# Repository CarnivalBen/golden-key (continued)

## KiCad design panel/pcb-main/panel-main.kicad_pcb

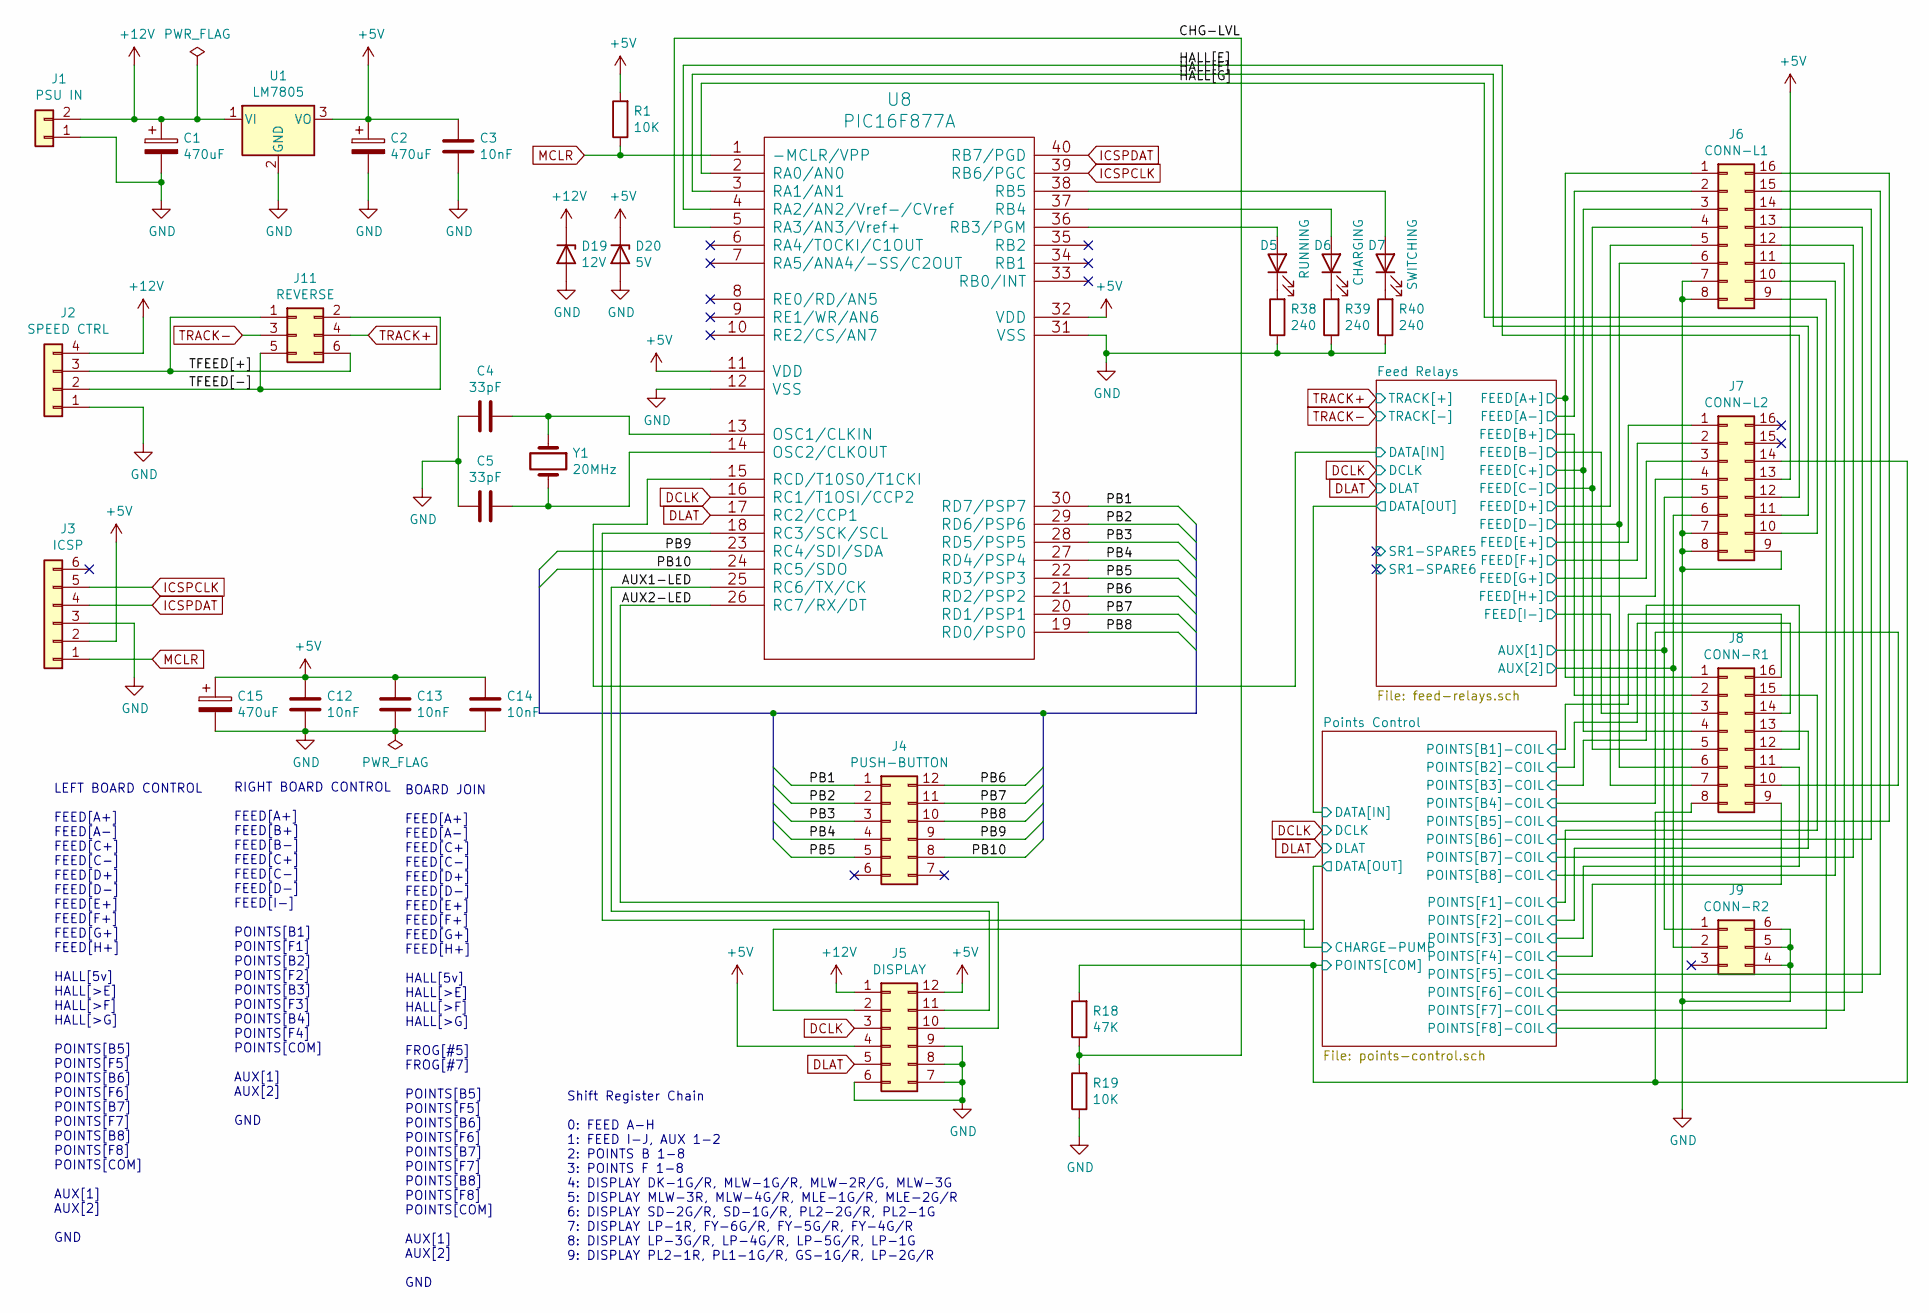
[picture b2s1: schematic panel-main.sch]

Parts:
C1, C2, C15: 470uF; CP_Radial_D10.0mm_P5.00mm
C3, C12, C13, C14: 10nF; C_Disc_D4.7mm_W2.5mm_P5.00mm
C4, C5: 33pF; C_Disc_D3.4mm_W2.1mm_P2.50mm
D5: RUNNING; LED_D5.0mm
D6: CHARGING; LED_D5.0mm
D7: SWITCHING; LED_D5.0mm
D19: 12V; D_DO-15_P10.16mm_Horizontal
D20: 5V; D_DO-15_P10.16mm_Horizontal
J1: PSU IN; Wire_Pads_Edge_1x2
J2: SPEED CTRL; DIN_Socket_Edge_Solder_4pin
J3: ICSP; Pin_Header_Straight_1x06_Pitch2.54mm
J4: PUSH-BUTTON; Pin_Header_Straight_2x06_Pitch2.54mm
J5: DISPLAY; Pin_Header_Straight_2x06_Pitch2.54mm
J6: CONN-L1; Wire_Pads_Edge_2x8
J7: CONN-L2; Wire_Pads_Edge_2x8
J8: CONN-R1; Wire_Pads_Edge_2x8
J9: CONN-R2; Wire_Pads_Edge_2x3
J11: REVERSE; Pin_Header_Straight_2x03_Pitch2.54mm
R1, R19: 10K; R_Axial_DIN0207_L6.3mm_D2.5mm_P10.16mm_Horizontal
R18: 47K; R_Axial_DIN0207_L6.3mm_D2.5mm_P10.16mm_Horizontal
R38, R39, R40: 240; R_Axial_DIN0207_L6.3mm_D2.5mm_P10.16mm_Horizontal
U1: LM7805; TO-220-3_Horizontal
U8: PIC16F877A; DIP-40_W15.24mm_LongPads
Y1: 20MHz; Crystal_HC49-U_Vertical

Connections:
+5V: C2.1, C3.1, C12.1, C13.1, C14.1, C15.1, D20.1 (K), J3.2, J5.4, J5.12, J7.13, R1.2, U1.3 (VO), U8.11 (VDD), U8.32 (VDD); also elsewhere on the board
+12V: C1.1, D19.1 (K), J1.2, J2.4, J5.1, U1.1 (VI); also elsewhere on the board
/AUX1-LED: J5.11, U8.25 (RC6/TX/CK)
/AUX2-LED: J5.10, U8.26 (RC7/RX/DT)
/CHG-LVL: R18.1, R19.2, U8.5 (RA3/AN3/Vref+)
/Feed Relays/AUX[1]: J7.5, J9.1; also elsewhere on the board
/Feed Relays/AUX[2]: J7.6, J9.2; also elsewhere on the board
/Feed Relays/DATA[IN]: U8.15 (RCD/T10S0/T1CKI); also elsewhere on the board
/Feed Relays/FEED[A+]: J6.1, J8.1; also elsewhere on the board
/Feed Relays/FEED[A-]: J6.2; also elsewhere on the board
/Feed Relays/FEED[B+]: J8.2; also elsewhere on the board
/Feed Relays/FEED[B-]: J8.3; also elsewhere on the board
/Feed Relays/FEED[C+]: J6.3, J8.4; also elsewhere on the board
/Feed Relays/FEED[C-]: J6.4, J8.5; also elsewhere on the board
/Feed Relays/FEED[D+]: J6.5; also elsewhere on the board
/Feed Relays/FEED[D-]: J6.6, J8.6; also elsewhere on the board
/Feed Relays/FEED[E+]: J7.1; also elsewhere on the board
/Feed Relays/FEED[F+]: J7.2; also elsewhere on the board
/Feed Relays/FEED[G+]: J7.3; also elsewhere on the board
/Feed Relays/FEED[H+]: J7.4; also elsewhere on the board
/Feed Relays/FEED[I-]: J8.7; also elsewhere on the board
/HALL[E]: J7.12, U8.4 (RA2/AN2/Vref-/CVref)
/HALL[F]: J7.11, U8.3 (RA1/AN1)
/HALL[G]: J7.10, U8.2 (RA0/AN0)
/PB1: J4.1, U8.30 (RD7/PSP7)
/PB2: J4.2, U8.29 (RD6/PSP6)
/PB3: J4.3, U8.28 (RD5/PSP5)
/PB4: J4.4, U8.27 (RD4/PSP4)
/PB5: J4.5, U8.22 (RD3/PSP3)
/PB6: J4.12, U8.21 (RD2/PSP2)
/PB7: J4.11, U8.20 (RD1/PSP1)
/PB8: J4.10, U8.19 (RD0/PSP0)
/PB9: J4.9, U8.23 (RC4/SDI/SDA)
/PB10: J4.8, U8.24 (RC5/SDO)
/Points Control/CHARGE-PUMP: U8.18 (RC3/SCK/SCL); also elsewhere on the board
/Points Control/DATA[OUT]: J5.2; also elsewhere on the board
/Points Control/POINTS[B1]-COIL: J8.16; also elsewhere on the board
/Points Control/POINTS[B2]-COIL: J8.14; also elsewhere on the board
/Points Control/POINTS[B3]-COIL: J8.12; also elsewhere on the board
/Points Control/POINTS[B4]-COIL: J8.10; also elsewhere on the board
/Points Control/POINTS[B5]-COIL: J6.16; also elsewhere on the board
/Points Control/POINTS[B6]-COIL: J6.14; also elsewhere on the board
/Points Control/POINTS[B7]-COIL: J6.12; also elsewhere on the board
/Points Control/POINTS[B8]-COIL: J6.10; also elsewhere on the board
/Points Control/POINTS[COM]: J7.14, J8.8, R18.2; also elsewhere on the board
/Points Control/POINTS[F1]-COIL: J8.15; also elsewhere on the board
/Points Control/POINTS[F2]-COIL: J8.13; also elsewhere on the board
/Points Control/POINTS[F3]-COIL: J8.11; also elsewhere on the board
/Points Control/POINTS[F4]-COIL: J8.9; also elsewhere on the board
/Points Control/POINTS[F5]-COIL: J6.15; also elsewhere on the board
/Points Control/POINTS[F6]-COIL: J6.13; also elsewhere on the board
/Points Control/POINTS[F7]-COIL: J6.11; also elsewhere on the board
/Points Control/POINTS[F8]-COIL: J6.9; also elsewhere on the board
/TFEED[+]: J2.3, J11.1, J11.6
/TFEED[-]: J2.2, J11.2, J11.5
DCLK: J5.3, U8.16 (RC1/T1OSI/CCP2); also elsewhere on the board
DLAT: J5.5, U8.17 (RC2/CCP1); also elsewhere on the board
GND: C1.2, C2.2, C3.2, C4.2, C5.2, C12.2, C13.2, C14.2, C15.2, D19.2 (A), D20.2 (A), J1.1, J2.1, J3.3, J5.6, J5.7, J5.8, J5.9, J6.7, J6.8, J7.7, J7.8, J7.9, J9.4, J9.5, J9.6, R19.1, R38.1, R39.1, R40.1, U1.2 (GND), U8.12 (VSS), U8.31 (VSS); also elsewhere on the board
ICSPCLK: J3.5, U8.39 (RB6/PGC)
ICSPDAT: J3.4, U8.40 (RB7/PGD)
MCLR: J3.1, R1.1, U8.1 (-MCLR/VPP)
unnamed: C4.1, U8.13 (OSC1/CLKIN), Y1.1
unnamed: C5.1, U8.14 (OSC2/CLKOUT), Y1.2
unnamed: D5.1 (K), R38.2
unnamed: D5.2 (A), U8.36 (RB3/PGM)
unnamed: D6.1 (K), R39.2
unnamed: D6.2 (A), U8.37 (RB4)
unnamed: D7.1 (K), R40.2
unnamed: D7.2 (A), U8.38 (RB5)
TRACK+: J11.4; also elsewhere on the board
TRACK-: J11.3; also elsewhere on the board

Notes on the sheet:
Shift Register Chain 0: FEED A-H 1: FEED I-J, AUX 1-2 2: POINTS B 1-8 3: POINTS F 1-8 4: DISPLAY DK-1G/R, MLW-1G/R, MLW-2R/G, MLW-3G 5: DISPLAY MLW-3R, MLW-4G/R, MLE-1G/R, MLE-2G/R 6: DISPLAY SD-2G/R, SD-1G/R, PL2-2G/R, PL2-1G 7: DISPLAY LP-1R, FY-6G/R, FY-5G/R, FY-4G/R 8: DISPLAY LP-3G/R, LP-4G/R,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
LEFT BOARD CONTROL FEED[A+] FEED[A-] FEED[C+] FEED[C-] FEED[D+] FEED[D-] FEED[E+] FEED[F+] FEED[G+] FEED[H+] HALL[5v] HALL[>E] HALL[>F] HALL[>G] POINTS[B5] POINTS[F5] POINTS[B6] POINTS[F6] POINTS[B7] POINTS[F7] POINTS[B8] POINTS[F8] POINTS[COM] AUX[1] AUX[2] GND
RIGHT BOARD CONTROL FEED[A+] FEED[B+] FEED[B-] FEED[C+] FEED[C-] FEED[D-] FEED[I-] POINTS[B1] POINTS[F1] POINTS[B2] POINTS[F2] POINTS[B3] POINTS[F3] POINTS[B4] POINTS[F4] POINTS[COM] AUX[1] AUX[2] GND
BOARD JOIN FEED[A+] FEED[A-] FEED[C+] FEED[C-] FEED[D+] FEED[D-] FEED[E+] FEED[F+] FEED[G+] FEED[H+] HALL[5v] HALL[>E] HALL[>F] HALL[>G] FROG[#5] FROG[#7] POINTS[B5] POINTS[F5] POINTS[B6] POINTS[F6] POINTS[B7] POINTS[F7] POINTS[B8] POINTS[F8] POINTS[COM] AUX[1] AUX[2] GND

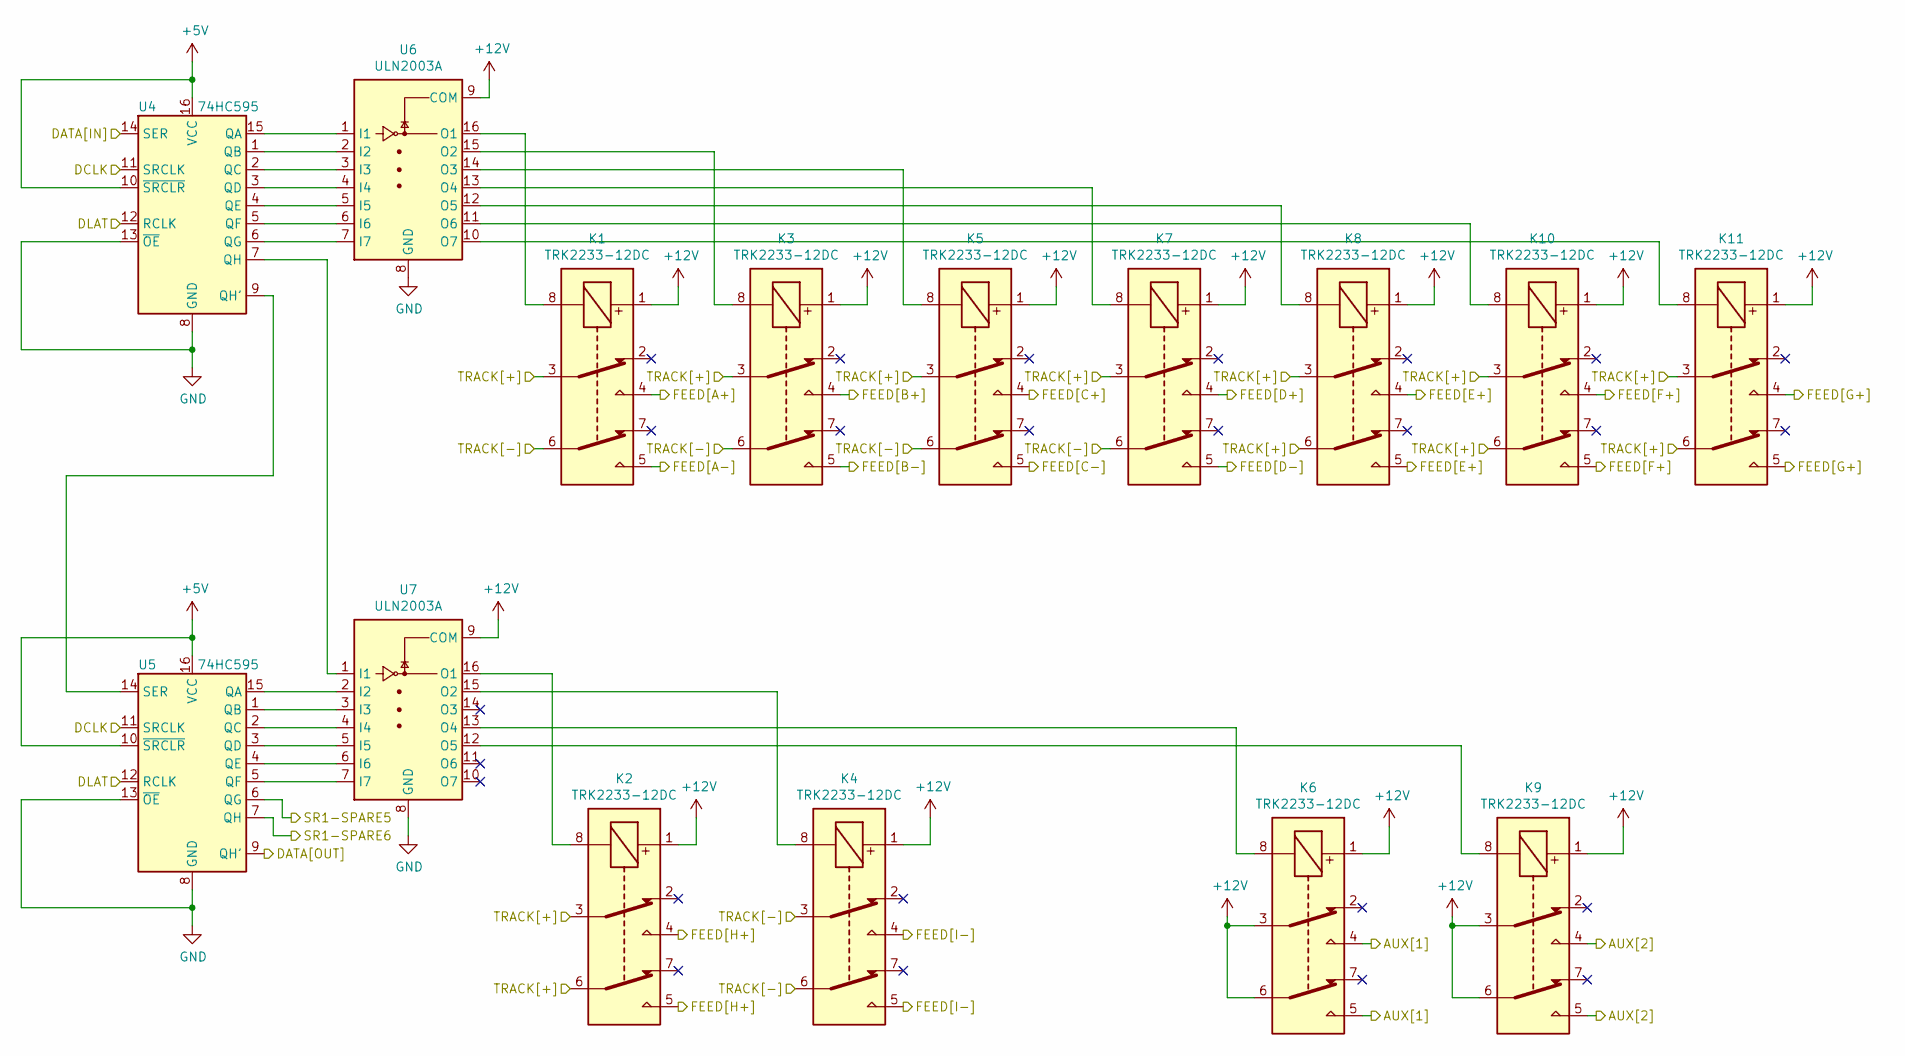
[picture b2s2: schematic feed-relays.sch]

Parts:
K1, K2, K3, K4, K5, K6, K7, K8, K9, K10, K11: TRK2233-12DC; TRK22X3-XXDC
U4, U5: 74HC595; DIP-16_W7.62mm_LongPads
U6, U7: ULN2003A; DIP-16_W7.62mm_LongPads

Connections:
+5V: U4.10 (~SRCLR), U4.16 (VCC), U5.10 (~SRCLR), U5.16 (VCC); also elsewhere on the board
+12V: K1.1, K2.1, K3.1, K4.1, K5.1, K6.1, K6.3, K6.6, K7.1, K8.1, K9.1, K9.3, K9.6, K10.1, K11.1, U6.9 (COM), U7.9 (COM); also elsewhere on the board
/Feed Relays/AUX[1]: K6.4, K6.5; also elsewhere on the board
/Feed Relays/AUX[2]: K9.4, K9.5; also elsewhere on the board
/Feed Relays/DATA[IN]: U4.14 (SER); also elsewhere on the board
/Feed Relays/FEED[A+]: K1.4; also elsewhere on the board
/Feed Relays/FEED[A-]: K1.5; also elsewhere on the board
/Feed Relays/FEED[B+]: K3.4; also elsewhere on the board
/Feed Relays/FEED[B-]: K3.5; also elsewhere on the board
/Feed Relays/FEED[C+]: K5.4; also elsewhere on the board
/Feed Relays/FEED[C-]: K5.5; also elsewhere on the board
/Feed Relays/FEED[D+]: K7.4; also elsewhere on the board
/Feed Relays/FEED[D-]: K7.5; also elsewhere on the board
/Feed Relays/FEED[E+]: K8.4, K8.5; also elsewhere on the board
/Feed Relays/FEED[F+]: K10.4, K10.5; also elsewhere on the board
/Feed Relays/FEED[G+]: K11.4, K11.5; also elsewhere on the board
/Feed Relays/FEED[H+]: K2.4, K2.5; also elsewhere on the board
/Feed Relays/FEED[I-]: K4.4, K4.5; also elsewhere on the board
/Feed Relays/SR1-SPARE5: U5.6 (QG)
/Feed Relays/SR1-SPARE6: U5.7 (QH)
/Points Control/DATA[IN]: U5.9 (QH'); also elsewhere on the board
DCLK: U4.11 (SRCLK), U5.11 (SRCLK); also elsewhere on the board
DLAT: U4.12 (RCLK), U5.12 (RCLK); also elsewhere on the board
GND: U4.8 (GND), U4.13 (~OE), U5.8 (GND), U5.13 (~OE), U6.8 (GND), U7.8 (GND); also elsewhere on the board
unnamed: K1.8, U6.16 (O1)
unnamed: K2.8, U7.16 (O1)
unnamed: K3.8, U6.15 (O2)
unnamed: K4.8, U7.15 (O2)
unnamed: K5.8, U6.14 (O3)
unnamed: K6.8, U7.13 (O4)
unnamed: K7.8, U6.13 (O4)
unnamed: K8.8, U6.12 (O5)
unnamed: K9.8, U7.12 (O5)
unnamed: K10.8, U6.11 (O6)
unnamed: K11.8, U6.10 (O7)
unnamed: U4.1 (QB), U6.2 (I2)
unnamed: U4.2 (QC), U6.3 (I3)
unnamed: U4.3 (QD), U6.4 (I4)
unnamed: U4.4 (QE), U6.5 (I5)
unnamed: U4.5 (QF), U6.6 (I6)
unnamed: U4.6 (QG), U6.7 (I7)
unnamed: U4.7 (QH), U7.1 (I1)
unnamed: U4.9 (QH'), U5.14 (SER)
unnamed: U4.15 (QA), U6.1 (I1)
unnamed: U5.1 (QB), U7.3 (I3)
unnamed: U5.2 (QC), U7.4 (I4)
unnamed: U5.3 (QD), U7.5 (I5)
unnamed: U5.4 (QE), U7.6 (I6)
unnamed: U5.5 (QF), U7.7 (I7)
unnamed: U5.15 (QA), U7.2 (I2)
TRACK+: K1.3, K2.3, K2.6, K3.3, K5.3, K7.3, K8.3, K8.6, K10.3, K10.6, K11.3, K11.6; also elsewhere on the board
TRACK-: K1.6, K3.6, K4.3, K4.6, K5.6, K7.6; also elsewhere on the board

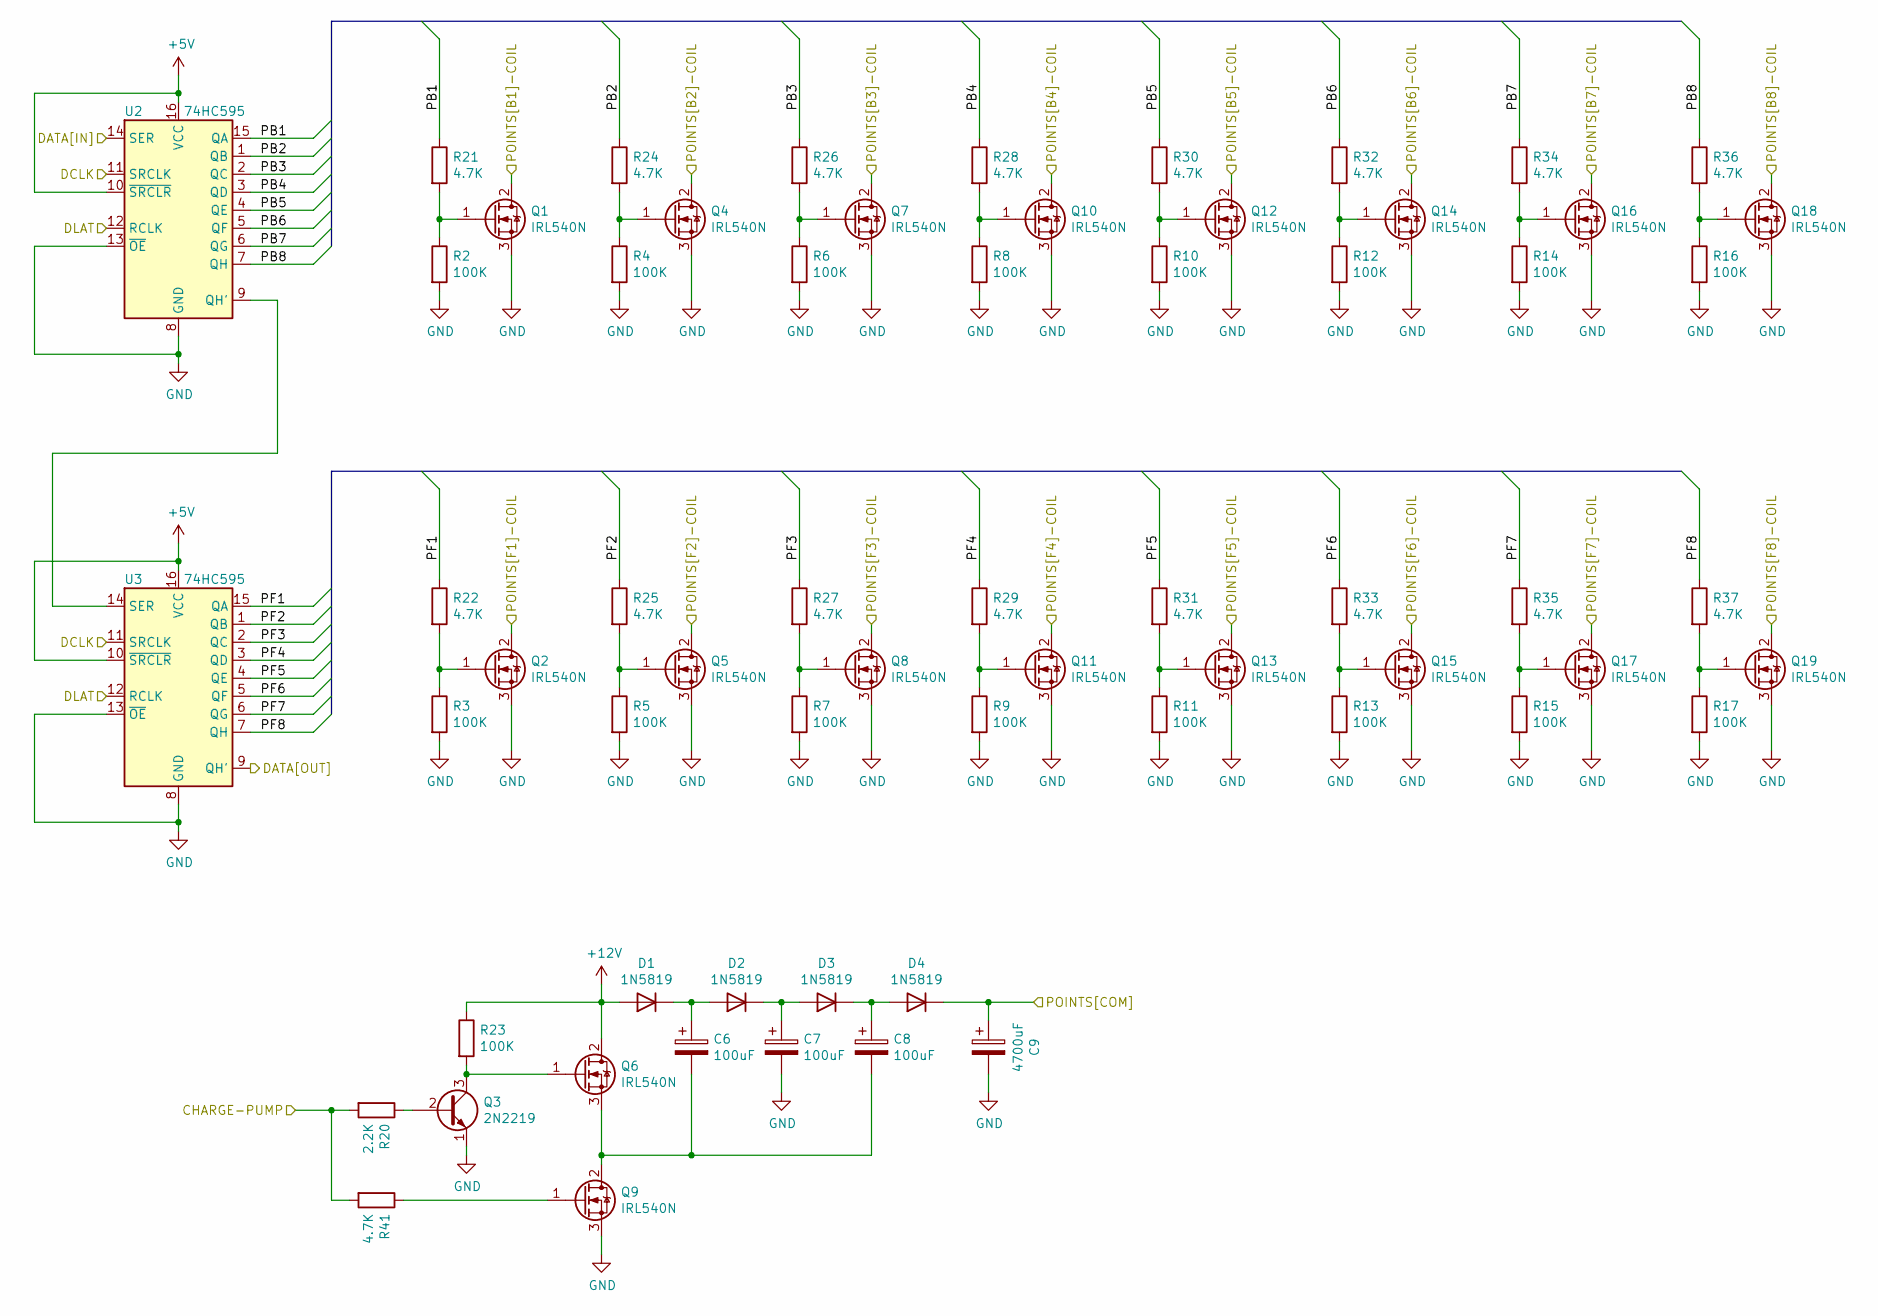
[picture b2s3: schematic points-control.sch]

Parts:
C6, C7, C8: 100uF; CP_Radial_D8.0mm_P2.50mm
C9: 4700uF; CP_Radial_D18.0mm_P7.50mm
D1, D2, D3, D4: 1N5819; D_DO-15_P12.70mm_Horizontal
Q1, Q2, Q4, Q5, Q6, Q7, Q8, Q9, Q10, Q11, Q12, Q13, Q14, Q15, Q16, Q17, Q18, Q19: IRL540N; TO-220-3_Horizontal
Q3: 2N2219; TO-92_Inline_Wide
R2, R3, R4, R5, R6, R7, R8, R9, R10, R11, R12, R13, R14, R15, R16, R17, R23: 100K; R_Axial_DIN0207_L6.3mm_D2.5mm_P10.16mm_Horizontal
R20: 2.2K; R_Axial_DIN0207_L6.3mm_D2.5mm_P10.16mm_Horizontal
R21, R22, R24, R25, R26, R27, R28, R29, R30, R31, R32, R33, R34, R35, R36, R37, R41: 4.7K; R_Axial_DIN0207_L6.3mm_D2.5mm_P10.16mm_Horizontal
U2, U3: 74HC595; DIP-16_W7.62mm_LongPads

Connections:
+5V: U2.10 (~SRCLR), U2.16 (VCC), U3.10 (~SRCLR), U3.16 (VCC); also elsewhere on the board
+12V: D1.2 (A), Q6.2 (D), R23.1; also elsewhere on the board
/Points Control/CHARGE-PUMP: R20.2, R41.2; also elsewhere on the board
/Points Control/DATA[IN]: U2.14 (SER); also elsewhere on the board
/Points Control/DATA[OUT]: U3.9 (QH'); also elsewhere on the board
/Points Control/PB1: R21.1, U2.15 (QA)
/Points Control/PB2: R24.1, U2.1 (QB)
/Points Control/PB3: R26.1, U2.2 (QC)
/Points Control/PB4: R28.1, U2.3 (QD)
/Points Control/PB5: R30.1, U2.4 (QE)
/Points Control/PB6: R32.1, U2.5 (QF)
/Points Control/PB7: R34.1, U2.6 (QG)
/Points Control/PB8: R36.1, U2.7 (QH)
/Points Control/PF1: R22.1, U3.15 (QA)
/Points Control/PF2: R25.1, U3.1 (QB)
/Points Control/PF3: R27.1, U3.2 (QC)
/Points Control/PF4: R29.1, U3.3 (QD)
/Points Control/PF5: R31.1, U3.4 (QE)
/Points Control/PF6: R33.1, U3.5 (QF)
/Points Control/PF7: R35.1, U3.6 (QG)
/Points Control/PF8: R37.1, U3.7 (QH)
/Points Control/POINTS[B1]-COIL: Q1.2 (D); also elsewhere on the board
/Points Control/POINTS[B2]-COIL: Q4.2 (D); also elsewhere on the board
/Points Control/POINTS[B3]-COIL: Q7.2 (D); also elsewhere on the board
/Points Control/POINTS[B4]-COIL: Q10.2 (D); also elsewhere on the board
/Points Control/POINTS[B5]-COIL: Q12.2 (D); also elsewhere on the board
/Points Control/POINTS[B6]-COIL: Q14.2 (D); also elsewhere on the board
/Points Control/POINTS[B7]-COIL: Q16.2 (D); also elsewhere on the board
/Points Control/POINTS[B8]-COIL: Q18.2 (D); also elsewhere on the board
/Points Control/POINTS[COM]: C9.1, D4.1 (K); also elsewhere on the board
/Points Control/POINTS[F1]-COIL: Q2.2 (D); also elsewhere on the board
/Points Control/POINTS[F2]-COIL: Q5.2 (D); also elsewhere on the board
/Points Control/POINTS[F3]-COIL: Q8.2 (D); also elsewhere on the board
/Points Control/POINTS[F4]-COIL: Q11.2 (D); also elsewhere on the board
/Points Control/POINTS[F5]-COIL: Q13.2 (D); also elsewhere on the board
/Points Control/POINTS[F6]-COIL: Q15.2 (D); also elsewhere on the board
/Points Control/POINTS[F7]-COIL: Q17.2 (D); also elsewhere on the board
/Points Control/POINTS[F8]-COIL: Q19.2 (D); also elsewhere on the board
DCLK: U2.11 (SRCLK), U3.11 (SRCLK); also elsewhere on the board
DLAT: U2.12 (RCLK), U3.12 (RCLK); also elsewhere on the board
GND: C7.2, C9.2, Q1.3 (S), Q2.3 (S), Q3.1 (E), Q4.3 (S), Q5.3 (S), Q7.3 (S), Q8.3 (S), Q9.3 (S), Q10.3 (S), Q11.3 (S), Q12.3 (S), Q13.3 (S), Q14.3 (S), Q15.3 (S), Q16.3 (S), Q17.3 (S), Q18.3 (S), Q19.3 (S), R2.2, R3.2, R4.2, R5.2, R6.2, R7.2, R8.2, R9.2, R10.2, R11.2, R12.2, R13.2, R14.2, R15.2, R16.2, R17.2, U2.8 (GND), U2.13 (~OE), U3.8 (GND), U3.13 (~OE); also elsewhere on the board
unnamed: C6.1, D1.1 (K), D2.2 (A)
unnamed: C6.2, C8.2, Q6.3 (S), Q9.2 (D)
unnamed: C7.1, D2.1 (K), D3.2 (A)
unnamed: C8.1, D3.1 (K), D4.2 (A)
unnamed: Q1.1 (G), R2.1, R21.2
unnamed: Q2.1 (G), R3.1, R22.2
unnamed: Q3.2 (B), R20.1
unnamed: Q3.3 (C), Q6.1 (G), R23.2
unnamed: Q4.1 (G), R4.1, R24.2
unnamed: Q5.1 (G), R5.1, R25.2
unnamed: Q7.1 (G), R6.1, R26.2
unnamed: Q8.1 (G), R7.1, R27.2
unnamed: Q9.1 (G), R41.1
unnamed: Q10.1 (G), R8.1, R28.2
unnamed: Q11.1 (G), R9.1, R29.2
unnamed: Q12.1 (G), R10.1, R30.2
unnamed: Q13.1 (G), R11.1, R31.2
unnamed: Q14.1 (G), R12.1, R32.2
unnamed: Q15.1 (G), R13.1, R33.2
unnamed: Q16.1 (G), R14.1, R34.2
unnamed: Q17.1 (G), R15.1, R35.2
unnamed: Q18.1 (G), R16.1, R36.2
unnamed: Q19.1 (G), R17.1, R37.2
unnamed: U2.9 (QH'), U3.14 (SER)

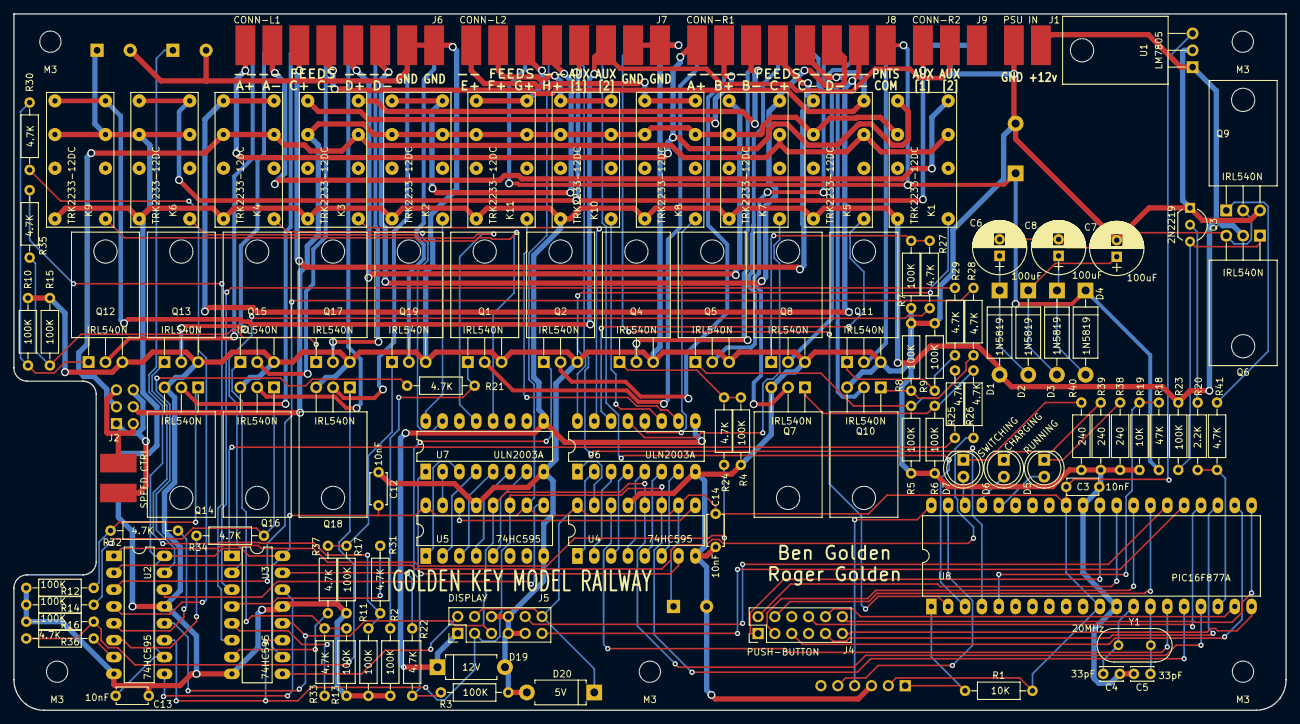
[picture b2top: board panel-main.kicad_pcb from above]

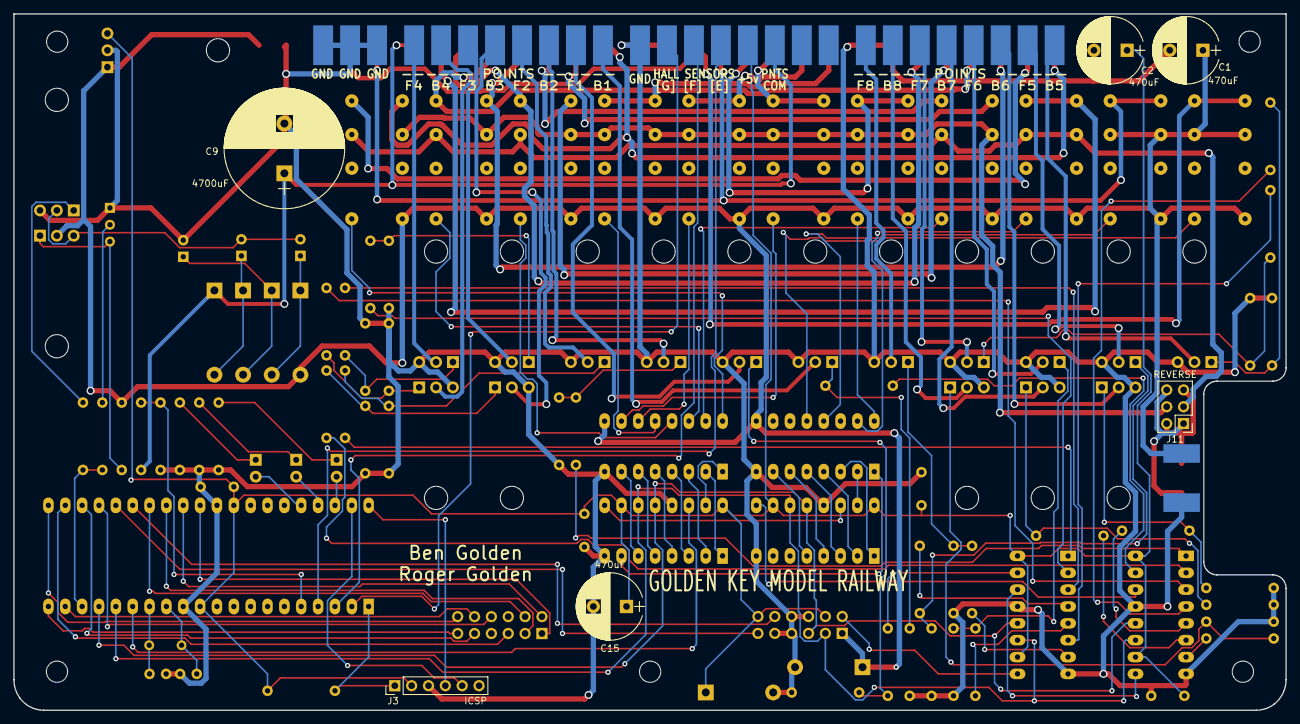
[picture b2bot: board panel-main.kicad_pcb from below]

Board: 2 copper layers, 191.7 x 104.9 mm, 112 parts (6 on the bottom side), 138 nets.

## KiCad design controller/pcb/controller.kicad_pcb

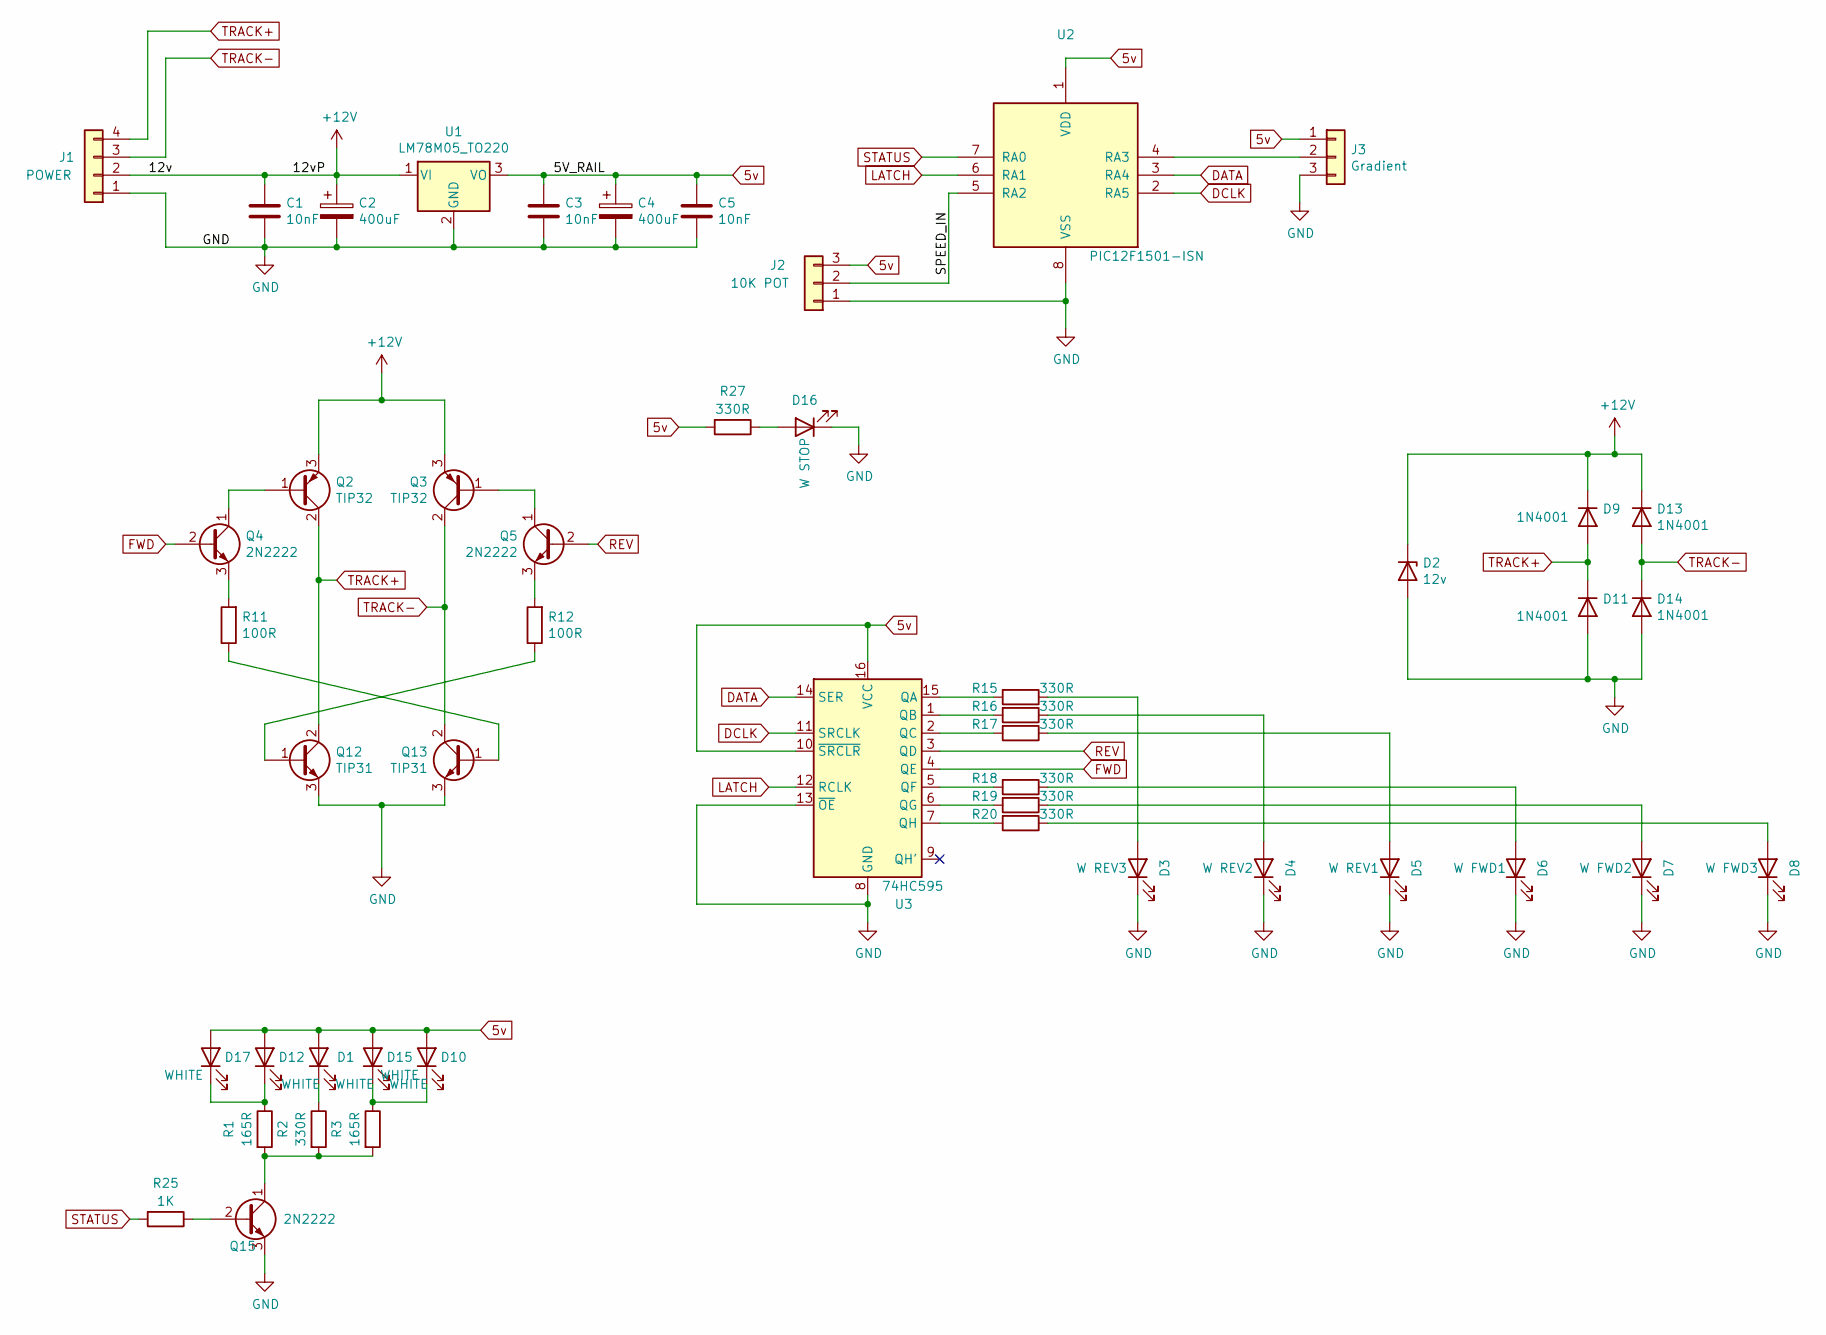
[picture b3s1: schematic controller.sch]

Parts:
C1, C3, C5: 10nF; C_Disc_D3.0mm_W1.6mm_P2.50mm
C2, C4: 400uF; CP_Radial_D6.3mm_P2.50mm
D1, D10, D12, D15, D17: WHITE; LED_D5.0mm
D2: 12v; D_A-405_P7.62mm_Horizontal
D3: W REV3; LED_D5.0mm
D4: W REV2; LED_D5.0mm
D5: W REV1; LED_D5.0mm
D6: W FWD1; LED_D5.0mm
D7: W FWD2; LED_D5.0mm
D8: W FWD3; LED_D5.0mm
D9, D11, D13, D14: 1N4001; D_A-405_P7.62mm_Horizontal
D16: W STOP; LED_D5.0mm
J1: POWER; Barrier_Terminal_P8.27_1x4
J2: 10K POT; Potentiometer_WirePads_Small
J3: Gradient; Pin_Header_Straight_1x03_Pitch2.54mm
Q2, Q3: TIP32; TO-220-3_Horizontal
Q4, Q5, Q15: 2N2222; TO-92_Inline_Wide
Q12, Q13: TIP31; TO-220-3_Horizontal
R1, R3: 165R; R_Axial_DIN0411_L9.9mm_D3.6mm_P12.70mm_Horizontal
R2, R15, R16, R17, R18, R19, R20, R27: 330R; R_Axial_DIN0411_L9.9mm_D3.6mm_P12.70mm_Horizontal
R11, R12: 100R; R_Axial_DIN0411_L9.9mm_D3.6mm_P12.70mm_Horizontal
R25: 1K; R_Axial_DIN0411_L9.9mm_D3.6mm_P12.70mm_Horizontal
U1: LM78M05_TO220; TO-220-3_Horizontal
U2: PIC12F1501-ISN; DIP-8_W7.62mm_Socket_LongPads
U3: 74HC595; DIP-16_W7.62mm_Socket_LongPads

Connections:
5v: C3.1, C4.1, C5.1, D1.2 (A), D10.2 (A), D12.2 (A), D15.2 (A), D17.2 (A), J2.3, J3.1, R27.2, U1.3 (VO), U2.1 (VDD), U3.10 (~SRCLR), U3.16 (VCC)
+12V: C1.1, C2.1, D2.1 (K), D9.1 (K), D13.1 (K), J1.2, Q2.3 (E), Q3.3 (E), U1.1 (VI)
/SPEED_IN: J2.2, U2.5 (RA2)
DATA: U2.3 (RA4), U3.14 (SER)
DCLK: U2.2 (RA5), U3.11 (SRCLK)
FWD: Q4.2 (B), U3.4 (QE)
GND: C1.2, C2.2, C3.2, C4.2, C5.2, D2.2 (A), D3.1 (K), D4.1 (K), D5.1 (K), D6.1 (K), D7.1 (K), D8.1 (K), D11.2 (A), D14.2 (A), D16.1 (K), J1.1, J2.1, J3.3, Q12.3 (E), Q13.3 (E), Q15.3 (E), U1.2 (GND), U2.8 (VSS), U3.8 (GND), U3.13 (~OE)
LATCH: U2.6 (RA1), U3.12 (RCLK)
unnamed: D1.1 (K), R2.1
unnamed: D3.2 (A), R15.1
unnamed: D4.2 (A), R16.1
unnamed: D5.2 (A), R17.1
unnamed: D6.2 (A), R18.1
unnamed: D7.2 (A), R19.1
unnamed: D8.2 (A), R20.1
unnamed: D10.1 (K), D15.1 (K), R3.1
unnamed: D12.1 (K), D17.1 (K), R1.1
unnamed: D16.2 (A), R27.1
unnamed: J3.2, U2.4 (RA3)
unnamed: Q2.1 (B), Q4.1 (C)
unnamed: Q3.1 (B), Q5.1 (C)
unnamed: Q4.3 (E), R11.2
unnamed: Q5.3 (E), R12.2
unnamed: Q12.1 (B), R12.1
unnamed: Q13.1 (B), R11.1
unnamed: Q15.1 (C), R1.2, R2.2, R3.2
unnamed: Q15.2 (B), R25.1
unnamed: R15.2, U3.15 (QA)
unnamed: R16.2, U3.1 (QB)
unnamed: R17.2, U3.2 (QC)
unnamed: R18.2, U3.5 (QF)
unnamed: R19.2, U3.6 (QG)
unnamed: R20.2, U3.7 (QH)
REV: Q5.2 (B), U3.3 (QD)
STATUS: R25.2, U2.7 (RA0)
TRACK+: D9.2 (A), D11.1 (K), J1.4, Q2.2 (C), Q12.2 (C)
TRACK-: D13.2 (A), D14.1 (K), J1.3, Q3.2 (C), Q13.2 (C)
